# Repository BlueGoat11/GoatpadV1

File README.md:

# GoatPad V1

This is my macro pad designed for gaming and fun shortcuts. It has 7 keys and an oled screen. I plan to use this for lots more than intially coded, but I'm happy with what I have now.

---

## Images

### Full Board (Top View)

### 3D Model Render

### Schematic

### PCB Layout

---

## jlcpcb.com estimate

---

##(BOM)

| Item | Qty | Description 
|------|-----|-------------|
| XIAO RP2040 | 1 | Main controller |
| 0.91" 128x32 OLED Display | 1 | OLED Screen |
| Cherry MX Switches | 7 | Key switches |
| DSA Keycaps| 7 | Keycaps for the switches |
| Case | 1 | Two 3D printed parts |

---

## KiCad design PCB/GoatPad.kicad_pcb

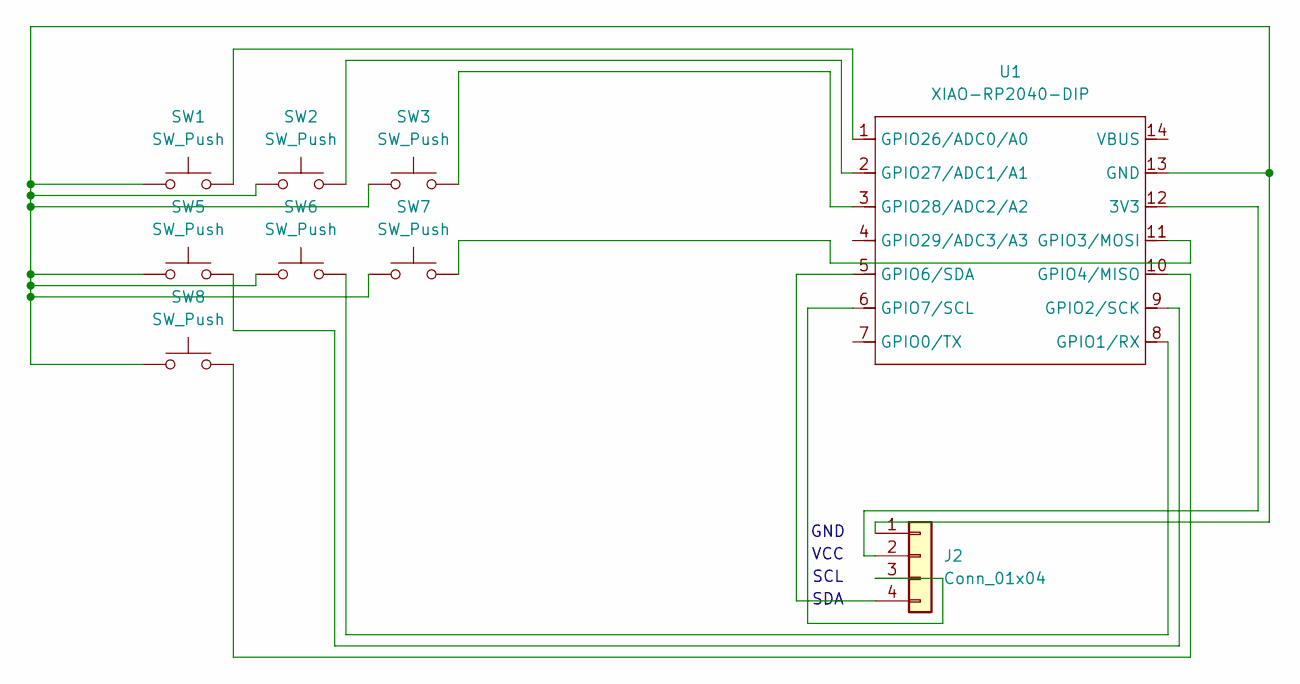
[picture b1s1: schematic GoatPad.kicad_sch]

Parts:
J2: Conn_01x04; SSD1306-0.91-OLED-4pin-128x32
SW1, SW2, SW3, SW5, SW6, SW7, SW8: SW_Push; SW_Cherry_MX_1.00u_PCB
U1: XIAO-RP2040-DIP

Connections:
unnamed: J2.1, SW1.1, SW2.1, SW3.1, SW5.1, SW6.1, SW7.1, SW8.1, U1.13 (GND)
unnamed: J2.2, U1.12 (3V3)
unnamed: J2.3, U1.6 (GPIO7/SCL)
unnamed: J2.4, U1.5 (GPIO6/SDA)
unnamed: SW6.2, U1.8 (GPIO1/RX)
unnamed: SW5.2, U1.9 (GPIO2/SCK)
unnamed: SW7.2, U1.11 (GPIO3/MOSI)
unnamed: SW8.2, U1.10 (GPIO4/MISO)
unnamed: SW1.2, U1.1 (GPIO26/ADC0/A0)
unnamed: SW2.2, U1.2 (GPIO27/ADC1/A1)
unnamed: SW3.2, U1.3 (GPIO28/ADC2/A2)

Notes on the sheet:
SCL
SDA
GND
VCC

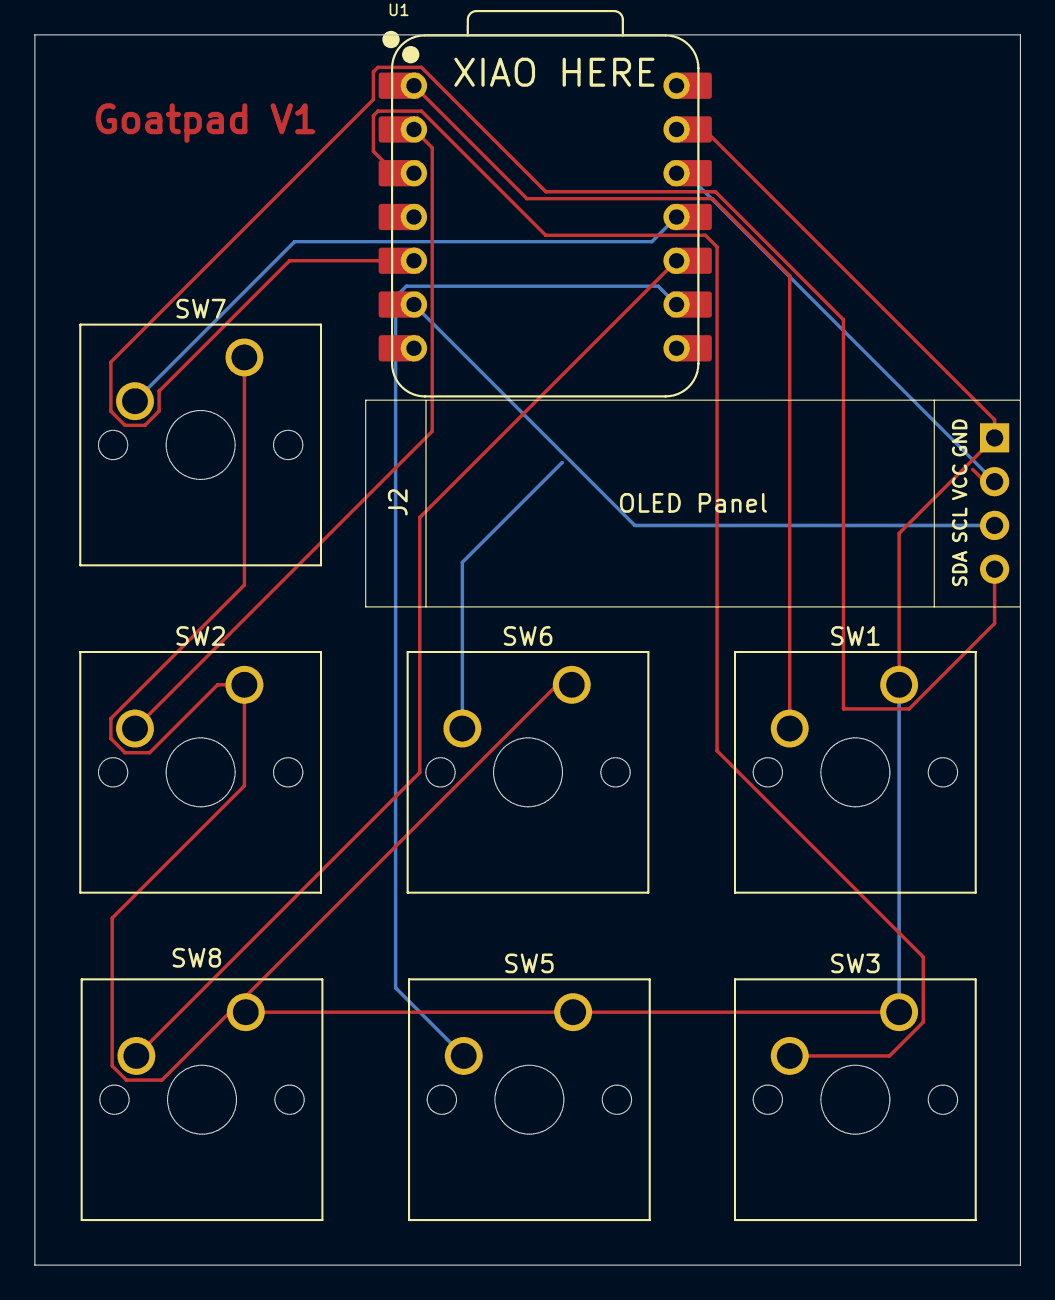
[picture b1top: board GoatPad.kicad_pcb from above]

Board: 2 copper layers, 57.2 x 71.4 mm, 9 parts (0 on the bottom side), 11 nets.

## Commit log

2026-01-01 Revise README for clarity and formatting
2026-01-01 Revise README for GoatPad V1
    Updated project name and description in README.md. Removed detailed features and assembly notes sections for brevity.
2026-01-01 Update BOM with revised item descriptions
2026-01-01 Refactor section headings in README.md
    Updated section headings in README for consistency.
2026-01-05 Fix for STL glitching in F360
2026-01-06 Added production folder and gerbers
2026-01-06 perfectionist ahh
